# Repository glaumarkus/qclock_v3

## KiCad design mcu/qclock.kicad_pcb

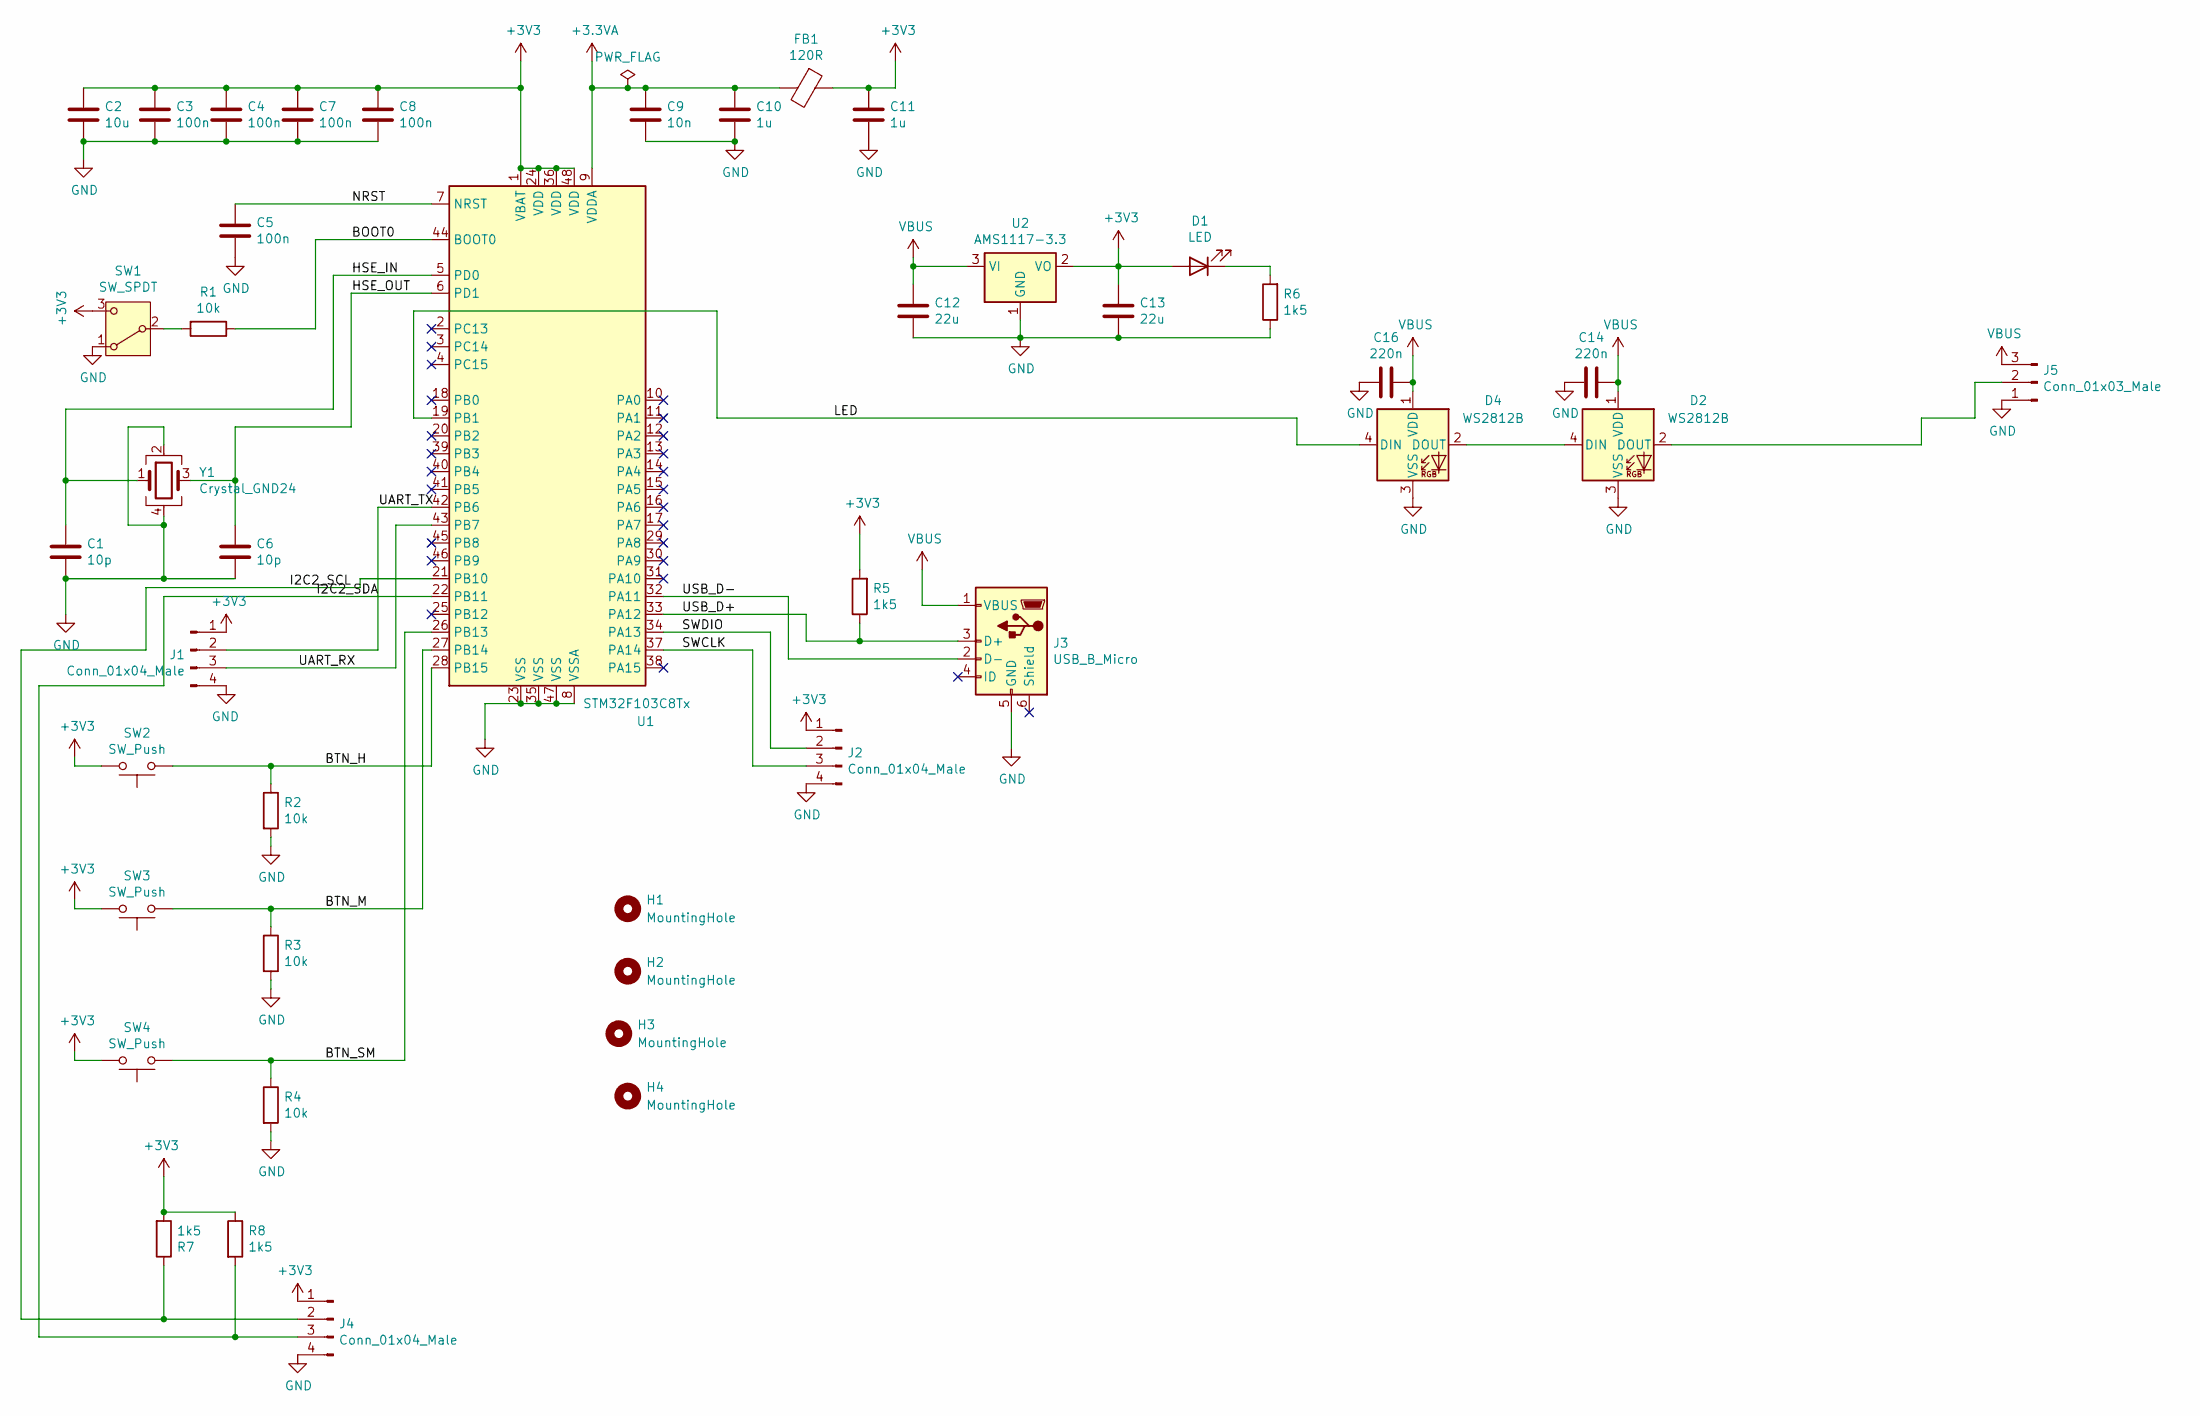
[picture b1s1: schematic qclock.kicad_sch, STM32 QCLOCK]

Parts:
C1, C6: 10p; C_0402_1005Metric
C2: 10u; C_0603_1608Metric
C3, C4, C5, C7, C8: 100n; C_0402_1005Metric
C9: 10n; C_0402_1005Metric
C10, C11: 1u; C_0402_1005Metric
C12, C13: 22u; C_0805_2012Metric
C14, C16: 220n; C_0402_1005Metric
D1: LED; LED_0603_1608Metric; JLCPCB Part #（optional） C2290
D2, D4: WS2812B; LED_WS2812B_PLCC4_5.0x5.0mm_P3.2mm; JLCPCB Part #（optional） C2846931
FB1: 120R; L_0402_1005Metric; JLCPCB Part #（optional） C3015760
H1, H2, H3, H4: MountingHole; MountingHole_2.2mm_M2
J1, J2, J4: Conn_01x04_Male; PinHeader_1x04_P2.54mm_Vertical
J3: USB_B_Micro; CUS-12TB_NDC; JLCPCB Part #（optional） C40943
J5: Conn_01x03_Male; PinHeader_1x03_P2.54mm_Vertical
R1, R2, R3, R4: 10k; R_0402_1005Metric; JLCPCB Part #（optional） C25744
R5, R6, R7, R8: 1k5; R_0402_1005Metric
SW1: SW_SPDT; CUS-12TB_NDC; JLCPCB Part #（optional） C2921739
SW2, SW3, SW4: SW_Push; mybtn_smd; JLCPCB Part #（optional） C455109
U1: STM32F103C8Tx; LQFP-48_7x7mm_P0.5mm
U2: AMS1117-3.3; SOT-223-3_TabPin2
Y1: Crystal_GND24; Crystal_SMD_3225-4Pin_3.2x2.5mm; JLCPCB Part #（optional） C963553

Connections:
+3.3VA: C9.1, C10.1, FB1.2, U1.9 (VDDA)
+3V3: C2.1, C3.1, C4.1, C7.1, C8.1, C11.1, C13.1, D1.2 (A), FB1.1, J1.1, J2.1, J4.1, R5.2, R7.2, R8.1, SW1.3 (C), SW2.2, SW3.2, SW4.2, U1.1 (VBAT), U1.24 (VDD), U1.36 (VDD), U1.48 (VDD), U2.2 (VO)
/BOOT0: R1.1, U1.44 (BOOT0)
/BTN_H: R2.1, SW2.1, U1.28 (PB15)
/BTN_M: R3.1, SW3.1, U1.27 (PB14)
/BTN_SM: R4.1, SW4.1, U1.26 (PB13)
/HSE_IN: C1.1, U1.5 (PD0), Y1.1
/HSE_OUT: C6.1, U1.6 (PD1), Y1.3
/I2C2_SCL: J4.2, R7.1, U1.21 (PB10)
/I2C2_SDA: J4.3, R8.2, U1.22 (PB11)
/LED: D4.4 (DIN), U1.19 (PB1)
/NRST: C5.1, U1.7 (NRST)
/SWCLK: J2.3, U1.37 (PA14)
/SWDIO: J2.2, U1.34 (PA13)
/UART_RX: J1.3, U1.43 (PB7)
/UART_TX: J1.2, U1.42 (PB6)
/USB_D+: J3.3 (D+), R5.1, U1.33 (PA12)
/USB_D-: J3.2 (D-), U1.32 (PA11)
GND: C1.2, C2.2, C3.2, C4.2, C5.2, C6.2, C7.2, C8.2, C9.2, C10.2, C11.2, C12.2, C13.2, C14.2, C16.2, D2.3 (VSS), D4.3 (VSS), J1.4, J2.4, J3.5 (GND), J4.4, J5.1, R2.2, R3.2, R4.2, R6.1, SW1.1 (A), U1.8 (VSSA), U1.23 (VSS), U1.35 (VSS), U1.47 (VSS), U2.1 (GND), Y1.2, Y1.4
unnamed: D1.1 (K), R6.2
unnamed: D2.4 (DIN), D4.2 (DOUT)
unnamed: D2.2 (DOUT), J5.2
unnamed: R1.2, SW1.2 (B)
VBUS: C12.1, C14.1, C16.1, D2.1 (VDD), D4.1 (VDD), J3.1 (VBUS), J5.3, U2.3 (VI)

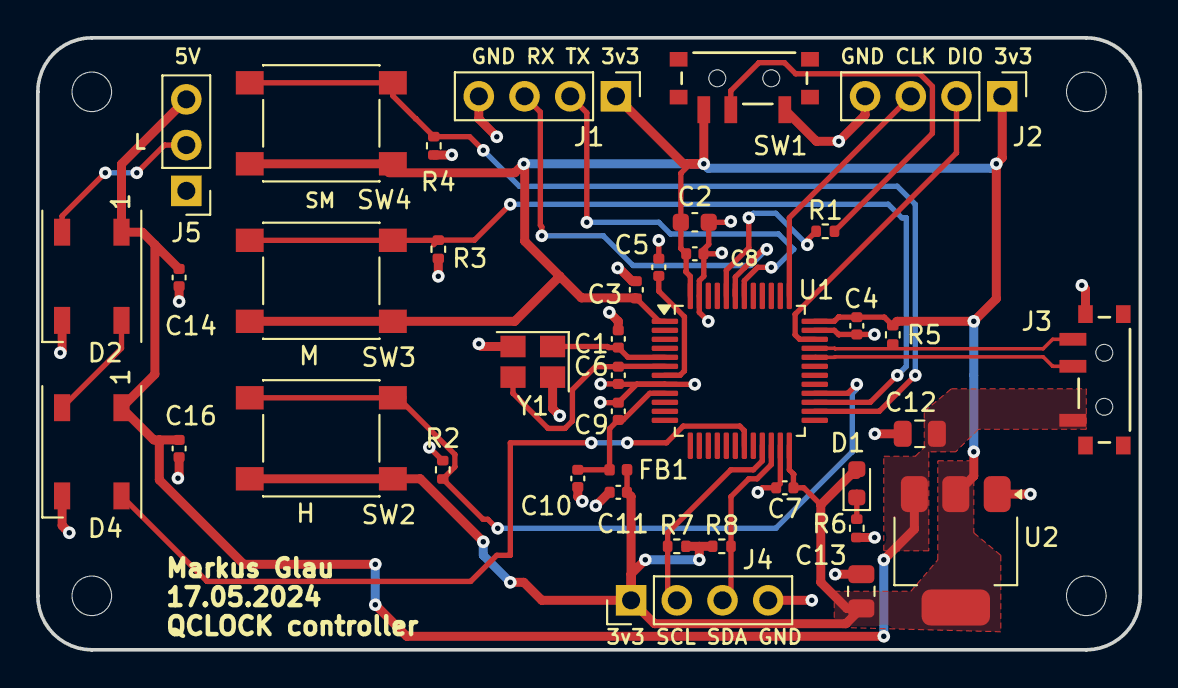
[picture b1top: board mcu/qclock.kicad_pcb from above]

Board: 2 copper layers, 61.2 x 34.0 mm, 43 parts (0 on the bottom side), 24 nets.

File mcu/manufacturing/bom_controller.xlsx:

Comment | Designator | Footprint | JLCPCB Part #（optional）
Crystal_GND24 | Y1 | Crystal:Crystal_SMD_3225-4Pin_3.2x2.5mm | C963553
AMS1117-3.3 | U2 | Package_TO_SOT_SMD:SOT-223-3_TabPin2
STM32F103C8Tx | U1 | Package_QFP:LQFP-48_7x7mm_P0.5mm
SW_Push | SW2,SW3,SW4 | btns:mybtn_smd | C455109
SW_SPDT | SW1 | footprints:CUS-12TB_NDC | C2921739
1k5 | R5,R6,R7,R8 | Resistor_SMD:R_0402_1005Metric
10k | R1,R2,R3,R4 | Resistor_SMD:R_0402_1005Metric | C25744
Conn_01x03_Male | J5 | Connector_PinHeader_2.54mm:PinHeader_1x03_P2.54mm_Vertical
USB_B_Micro | J3 | Connector_USB:USB_Micro-B_Wuerth_629105150521 | C879727
Conn_01x04_Male | J1,J2,J4 | Connector_PinHeader_2.54mm:PinHeader_1x04_P2.54mm_Vertical
120R | FB1 | Inductor_SMD:L_0402_1005Metric | C3015760
WS2812B | D2,D4 | LED_SMD:LED_WS2812B_PLCC4_5.0x5.0mm_P3.2mm | C2846931
LED | D1 | LED_SMD:LED_0603_1608Metric | C2290
220n | C14,C16 | Capacitor_SMD:C_0402_1005Metric
22u | C12,C13 | Capacitor_SMD:C_0805_2012Metric
1u | C10,C11 | Capacitor_SMD:C_0402_1005Metric
10n | C9 | Capacitor_SMD:C_0402_1005Metric
100n | C3,C4,C5,C7,C8 | Capacitor_SMD:C_0402_1005Metric
10u | C2 | Capacitor_SMD:C_0603_1608Metric
10p | C1,C6 | Capacitor_SMD:C_0402_1005Metric

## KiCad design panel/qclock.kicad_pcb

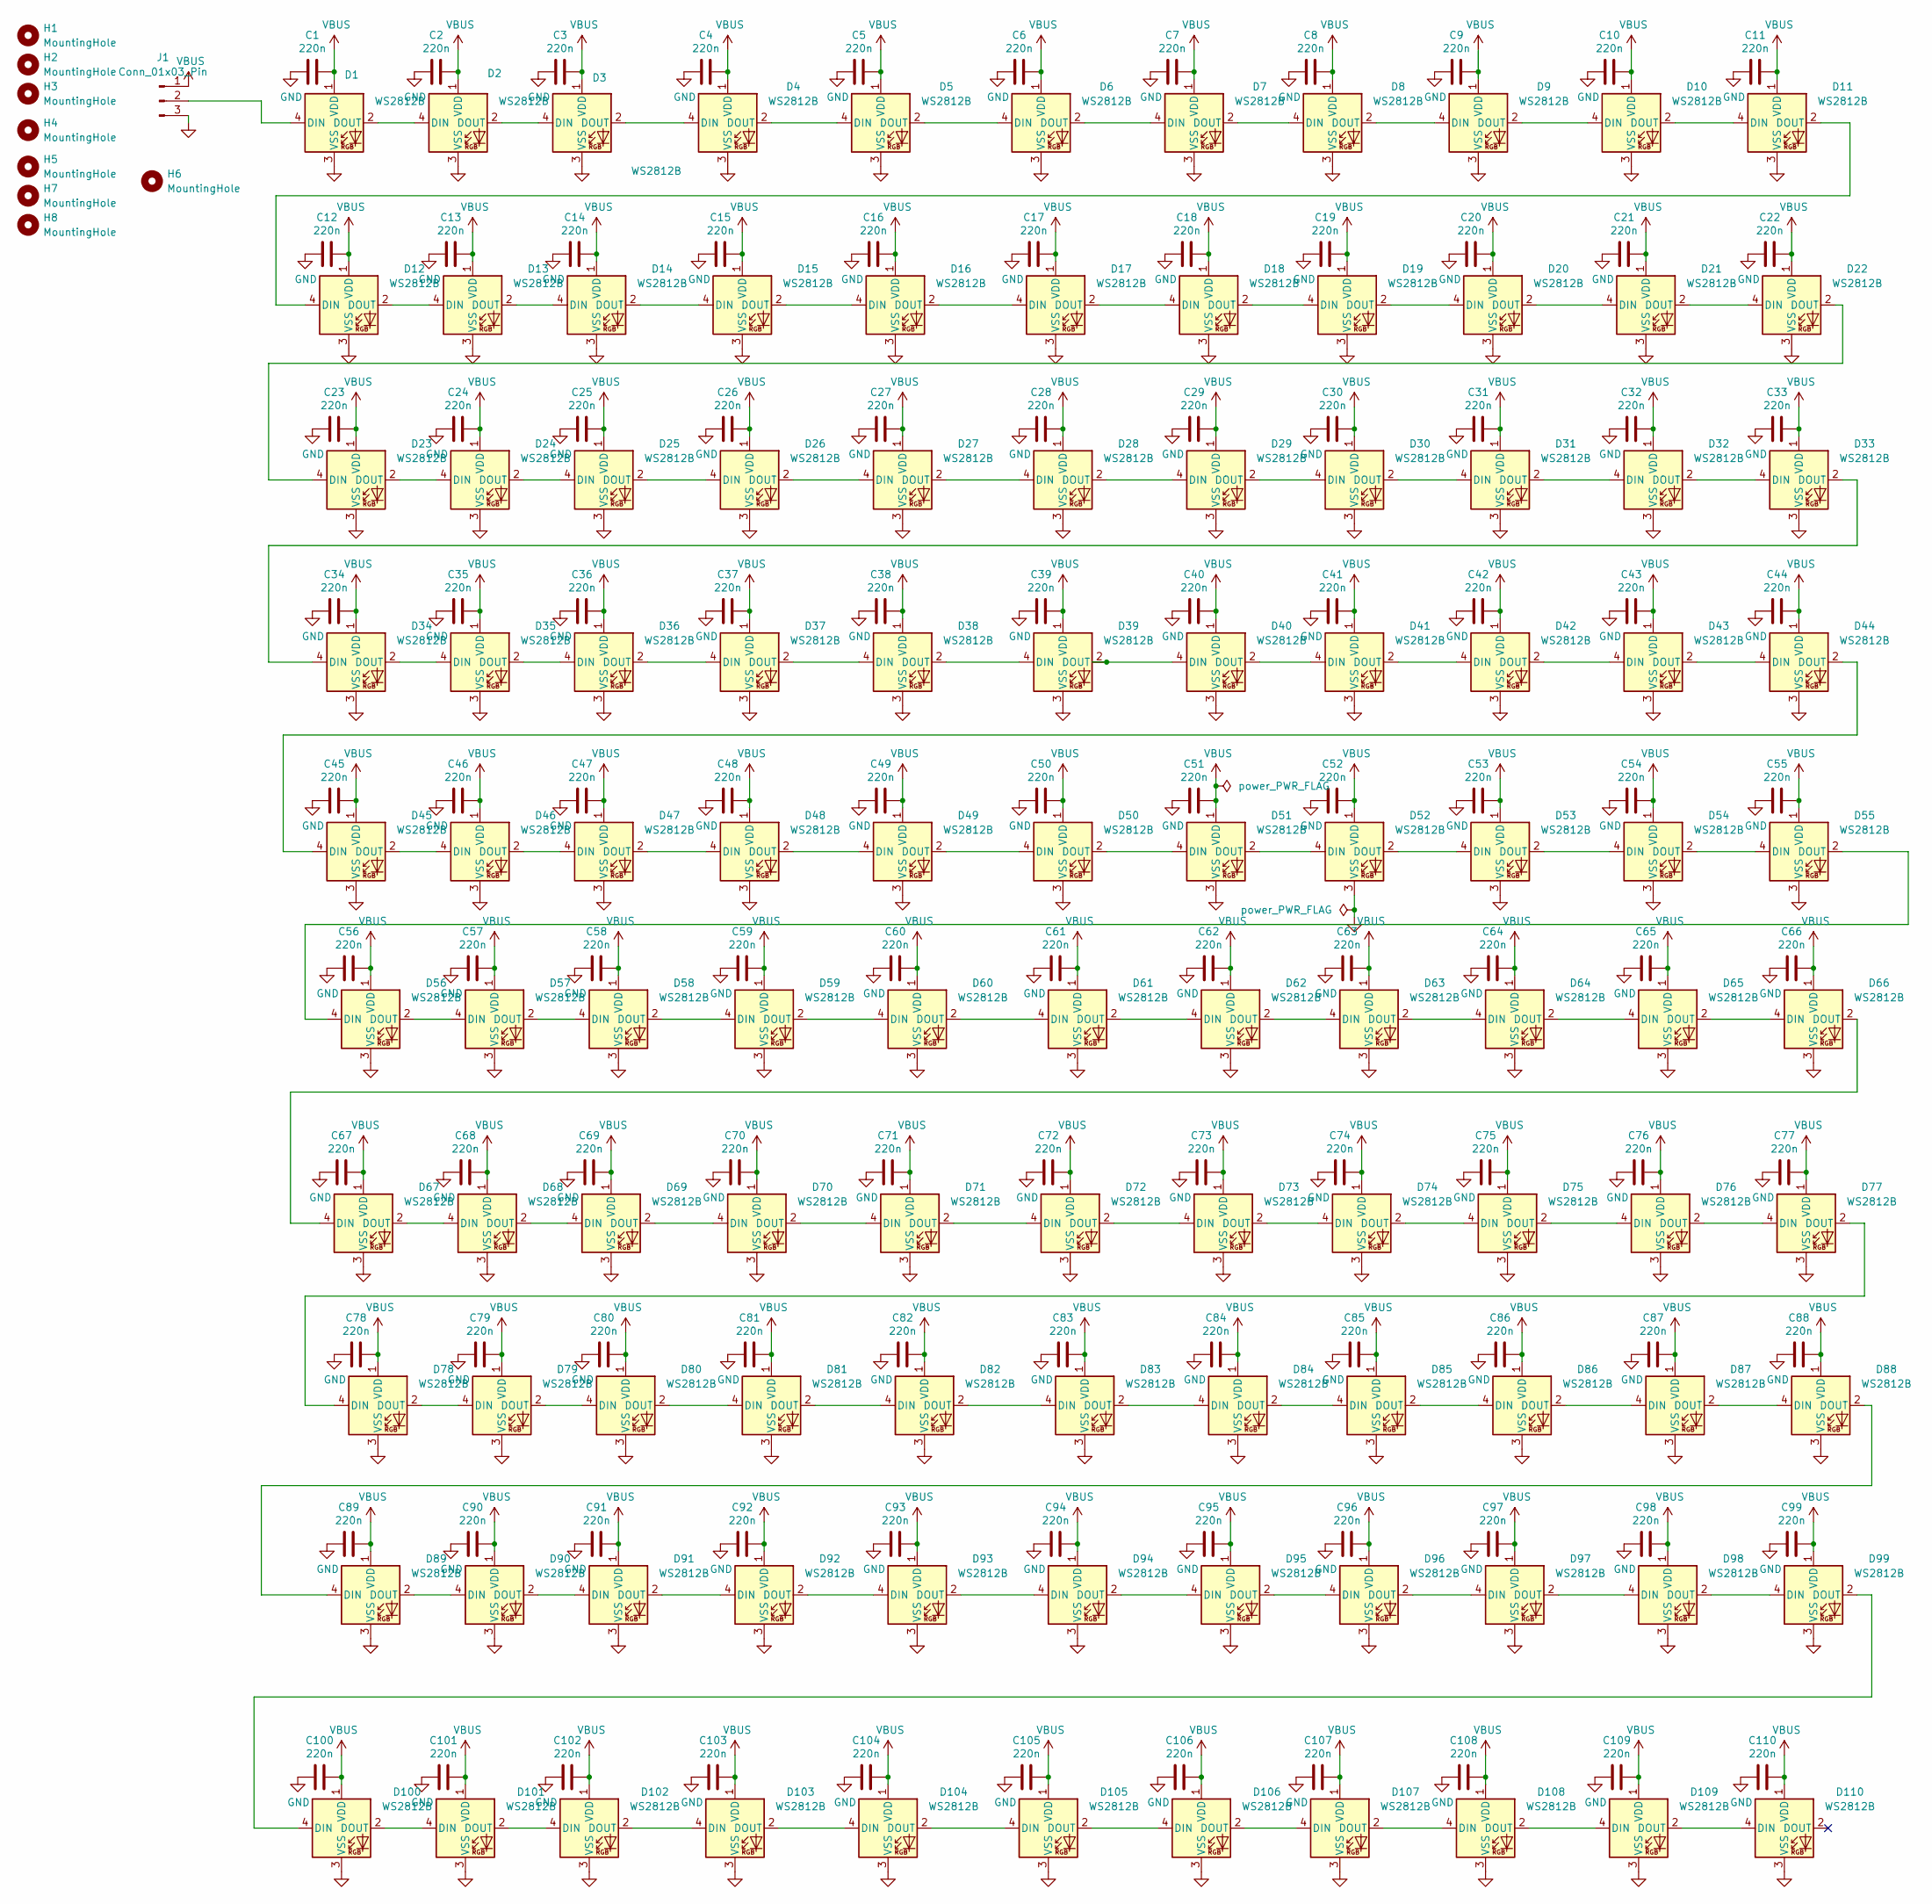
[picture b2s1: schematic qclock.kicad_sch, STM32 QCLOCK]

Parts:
C1, C2, C3, C4, C5, C6, C7, C8, C9, C10, C11, C12, C13, C14, C15, C16, C17, C18, C19, C20, C21, C22, C23, C24, C25, C26, C27, C28, C29, C30, C31, C32, C33, C34, C35, C36, C37, C38, C39, C40, C41, C42, C43, C44, C45, C46, C47, C48, C49, C50, C51, C52, C53, C54, C55, C56, C57, C58, C59, C60, C61, C62, C63, C64, C65, C66, C67, C68, C69, C70, C71, C72, C73, C74, C75, C76, C77, C78, C79, C80, C81, C82, C83, C84, C85, C86, C87, C88, C89, C90, C91, C92, C93, C94, C95, C96, C97, C98, C99, C100, C101, C102, C103, C104, C105, C106, C107, C108, C109, C110: 220n; C_0402_1005Metric
D1, D2, D3, D4, D5, D6, D7, D8, D9, D10, D11, D12, D13, D14, D15, D16, D17, D18, D19, D20, D21, D22, D23, D24, D25, D26, D27, D28, D29, D30, D31, D32, D33, D34, D35, D36, D37, D38, D39, D40, D41, D42, D43, D44, D45, D46, D47, D48, D49, D50, D51, D52, D53, D54, D55, D56, D57, D58, D59, D60, D61, D62, D63, D64, D65, D66, D67, D68, D69, D70, D71, D72, D73, D74, D75, D76, D77, D78, D79, D80, D81, D82, D83, D84, D85, D86, D87, D88, D89, D90, D91, D92, D93, D94, D95, D96, D97, D98, D99, D100, D101, D102, D103, D104, D105, D106, D107, D108, D109, D110: WS2812B; LED_WS2812B_PLCC4_5.0x5.0mm_P3.2mm
H1, H2, H3, H4: MountingHole; MountingHole_2.2mm_M2
H5, H6, H7, H8: MountingHole; MountingHole_3.2mm_M3
J1: Conn_01x03_Pin; PinHeader_1x03_P2.54mm_Horizontal

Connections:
GND: C1.2, C2.2, C3.2, C4.2, C5.2, C6.2, C7.2, C8.2, C9.2, C10.2, C11.2, C12.2, C13.2, C14.2, C15.2, C16.2, C17.2, C18.2, C19.2, C20.2, C21.2, C22.2, C23.2, C24.2, C25.2, C26.2, C27.2, C28.2, C29.2, C30.2, C31.2, C32.2, C33.2, C34.2, C35.2, C36.2, C37.2, C38.2, C39.2, C40.2, C41.2, C42.2, C43.2, C44.2, C45.2, C46.2, C47.2, C48.2, C49.2, C50.2, C51.2, C52.2, C53.2, C54.2, C55.2, C56.2, C57.2, C58.2, C59.2, C60.2, C61.2, C62.2, C63.2, C64.2, C65.2, C66.2, C67.2, C68.2, C69.2, C70.2, C71.2, C72.2, C73.2, C74.2, C75.2, C76.2, C77.2, C78.2, C79.2, C80.2, C81.2, C82.2, C83.2, C84.2, C85.2, C86.2, C87.2, C88.2, C89.2, C90.2, C91.2, C92.2, C93.2, C94.2, C95.2, C96.2, C97.2, C98.2, C99.2, C100.2, C101.2, C102.2, C103.2, C104.2, C105.2, C106.2, C107.2, C108.2, C109.2, C110.2, D1.3 (VSS), D2.3 (VSS), D3.3 (VSS), D4.3 (VSS), D5.3 (VSS), D6.3 (VSS), D7.3 (VSS), D8.3 (VSS), D9.3 (VSS), D10.3 (VSS), D11.3 (VSS), D12.3 (VSS), D13.3 (VSS), D14.3 (VSS), D15.3 (VSS), D16.3 (VSS), D17.3 (VSS), D18.3 (VSS), D19.3 (VSS), D20.3 (VSS), D21.3 (VSS), D22.3 (VSS), D23.3 (VSS), D24.3 (VSS), D25.3 (VSS), D26.3 (VSS), D27.3 (VSS), D28.3 (VSS), D29.3 (VSS), D30.3 (VSS), D31.3 (VSS), D32.3 (VSS), D33.3 (VSS), D34.3 (VSS), D35.3 (VSS), D36.3 (VSS), D37.3 (VSS), D38.3 (VSS), D39.3 (VSS), D40.3 (VSS), D41.3 (VSS), D42.3 (VSS), D43.3 (VSS), D44.3 (VSS), D45.3 (VSS), D46.3 (VSS), D47.3 (VSS), D48.3 (VSS), D49.3 (VSS), D50.3 (VSS), D51.3 (VSS), D52.3 (VSS), D53.3 (VSS), D54.3 (VSS), D55.3 (VSS), D56.3 (VSS), D57.3 (VSS), D58.3 (VSS), D59.3 (VSS), D60.3 (VSS), D61.3 (VSS), D62.3 (VSS), D63.3 (VSS), D64.3 (VSS), D65.3 (VSS), D66.3 (VSS), D67.3 (VSS), D68.3 (VSS), D69.3 (VSS), D70.3 (VSS), D71.3 (VSS), D72.3 (VSS), D73.3 (VSS), D74.3 (VSS), D75.3 (VSS), D76.3 (VSS), D77.3 (VSS), D78.3 (VSS), D79.3 (VSS), D80.3 (VSS), D81.3 (VSS), D82.3 (VSS), D83.3 (VSS), D84.3 (VSS), D85.3 (VSS), D86.3 (VSS), D87.3 (VSS), D88.3 (VSS), D89.3 (VSS), D90.3 (VSS), D91.3 (VSS), D92.3 (VSS), D93.3 (VSS), D94.3 (VSS), D95.3 (VSS), D96.3 (VSS), D97.3 (VSS), D98.3 (VSS), D99.3 (VSS), D100.3 (VSS), D101.3 (VSS), D102.3 (VSS), D103.3 (VSS), D104.3 (VSS), D105.3 (VSS), D106.3 (VSS), D107.3 (VSS), D108.3 (VSS), D109.3 (VSS), D110.3 (VSS), J1.3
unnamed: D1.4 (DIN), J1.2
unnamed: D1.2 (DOUT), D2.4 (DIN)
unnamed: D2.2 (DOUT), D3.4 (DIN)
unnamed: D3.2 (DOUT), D4.4 (DIN)
unnamed: D4.2 (DOUT), D5.4 (DIN)
unnamed: D5.2 (DOUT), D6.4 (DIN)
unnamed: D6.2 (DOUT), D7.4 (DIN)
unnamed: D7.2 (DOUT), D8.4 (DIN)
unnamed: D8.2 (DOUT), D9.4 (DIN)
unnamed: D9.2 (DOUT), D10.4 (DIN)
unnamed: D10.2 (DOUT), D11.4 (DIN)
unnamed: D11.2 (DOUT), D12.4 (DIN)
unnamed: D12.2 (DOUT), D13.4 (DIN)
unnamed: D13.2 (DOUT), D14.4 (DIN)
unnamed: D14.2 (DOUT), D15.4 (DIN)
unnamed: D15.2 (DOUT), D16.4 (DIN)
unnamed: D16.2 (DOUT), D17.4 (DIN)
unnamed: D17.2 (DOUT), D18.4 (DIN)
unnamed: D18.2 (DOUT), D19.4 (DIN)
unnamed: D19.2 (DOUT), D20.4 (DIN)
unnamed: D20.2 (DOUT), D21.4 (DIN)
unnamed: D21.2 (DOUT), D22.4 (DIN)
unnamed: D22.2 (DOUT), D23.4 (DIN)
unnamed: D23.2 (DOUT), D24.4 (DIN)
unnamed: D24.2 (DOUT), D25.4 (DIN)
unnamed: D25.2 (DOUT), D26.4 (DIN)
unnamed: D26.2 (DOUT), D27.4 (DIN)
unnamed: D27.2 (DOUT), D28.4 (DIN)
unnamed: D28.2 (DOUT), D29.4 (DIN)
unnamed: D29.2 (DOUT), D30.4 (DIN)
unnamed: D30.2 (DOUT), D31.4 (DIN)
unnamed: D31.2 (DOUT), D32.4 (DIN)
unnamed: D32.2 (DOUT), D33.4 (DIN)
unnamed: D33.2 (DOUT), D34.4 (DIN)
unnamed: D34.2 (DOUT), D35.4 (DIN)
unnamed: D35.2 (DOUT), D36.4 (DIN)
unnamed: D36.2 (DOUT), D37.4 (DIN)
unnamed: D37.2 (DOUT), D38.4 (DIN)
unnamed: D38.2 (DOUT), D39.4 (DIN)
unnamed: D39.2 (DOUT), D40.4 (DIN)
unnamed: D40.2 (DOUT), D41.4 (DIN)
unnamed: D41.2 (DOUT), D42.4 (DIN)
unnamed: D42.2 (DOUT), D43.4 (DIN)
unnamed: D43.2 (DOUT), D44.4 (DIN)
unnamed: D44.2 (DOUT), D45.4 (DIN)
unnamed: D45.2 (DOUT), D46.4 (DIN)
unnamed: D46.2 (DOUT), D47.4 (DIN)
unnamed: D47.2 (DOUT), D48.4 (DIN)
unnamed: D48.2 (DOUT), D49.4 (DIN)
unnamed: D49.2 (DOUT), D50.4 (DIN)
unnamed: D50.2 (DOUT), D51.4 (DIN)
unnamed: D51.2 (DOUT), D52.4 (DIN)
unnamed: D52.2 (DOUT), D53.4 (DIN)
unnamed: D53.2 (DOUT), D54.4 (DIN)
unnamed: D54.2 (DOUT), D55.4 (DIN)
unnamed: D55.2 (DOUT), D56.4 (DIN)
unnamed: D56.2 (DOUT), D57.4 (DIN)
unnamed: D57.2 (DOUT), D58.4 (DIN)
unnamed: D58.2 (DOUT), D59.4 (DIN)
unnamed: D59.2 (DOUT), D60.4 (DIN)
unnamed: D60.2 (DOUT), D61.4 (DIN)
unnamed: D61.2 (DOUT), D62.4 (DIN)
unnamed: D62.2 (DOUT), D63.4 (DIN)
unnamed: D63.2 (DOUT), D64.4 (DIN)
unnamed: D64.2 (DOUT), D65.4 (DIN)
unnamed: D65.2 (DOUT), D66.4 (DIN)
unnamed: D66.2 (DOUT), D67.4 (DIN)
unnamed: D67.2 (DOUT), D68.4 (DIN)
unnamed: D68.2 (DOUT), D69.4 (DIN)
unnamed: D69.2 (DOUT), D70.4 (DIN)
unnamed: D70.2 (DOUT), D71.4 (DIN)
unnamed: D71.2 (DOUT), D72.4 (DIN)
unnamed: D72.2 (DOUT), D73.4 (DIN)
unnamed: D73.2 (DOUT), D74.4 (DIN)
unnamed: D74.2 (DOUT), D75.4 (DIN)
unnamed: D75.2 (DOUT), D76.4 (DIN)
unnamed: D76.2 (DOUT), D77.4 (DIN)
unnamed: D77.2 (DOUT), D78.4 (DIN)
unnamed: D78.2 (DOUT), D79.4 (DIN)
unnamed: D79.2 (DOUT), D80.4 (DIN)
unnamed: D80.2 (DOUT), D81.4 (DIN)
unnamed: D81.2 (DOUT), D82.4 (DIN)
unnamed: D82.2 (DOUT), D83.4 (DIN)
unnamed: D83.2 (DOUT), D84.4 (DIN)
unnamed: D84.2 (DOUT), D85.4 (DIN)
unnamed: D85.2 (DOUT), D86.4 (DIN)
unnamed: D86.2 (DOUT), D87.4 (DIN)
unnamed: D87.2 (DOUT), D88.4 (DIN)
unnamed: D88.2 (DOUT), D89.4 (DIN)
unnamed: D89.2 (DOUT), D90.4 (DIN)
unnamed: D90.2 (DOUT), D91.4 (DIN)
unnamed: D91.2 (DOUT), D92.4 (DIN)
unnamed: D92.2 (DOUT), D93.4 (DIN)
unnamed: D93.2 (DOUT), D94.4 (DIN)
unnamed: D94.2 (DOUT), D95.4 (DIN)
unnamed: D95.2 (DOUT), D96.4 (DIN)
unnamed: D96.2 (DOUT), D97.4 (DIN)
unnamed: D97.2 (DOUT), D98.4 (DIN)
unnamed: D98.2 (DOUT), D99.4 (DIN)
unnamed: D99.2 (DOUT), D100.4 (DIN)
unnamed: D100.2 (DOUT), D101.4 (DIN)
unnamed: D101.2 (DOUT), D102.4 (DIN)
unnamed: D102.2 (DOUT), D103.4 (DIN)
unnamed: D103.2 (DOUT), D104.4 (DIN)
unnamed: D104.2 (DOUT), D105.4 (DIN)
unnamed: D105.2 (DOUT), D106.4 (DIN)
unnamed: D106.2 (DOUT), D107.4 (DIN)
unnamed: D107.2 (DOUT), D108.4 (DIN)
unnamed: D108.2 (DOUT), D109.4 (DIN)
unnamed: D109.2 (DOUT), D110.4 (DIN)
VBUS: C1.1, C2.1, C3.1, C4.1, C5.1, C6.1, C7.1, C8.1, C9.1, C10.1, C11.1, C12.1, C13.1, C14.1, C15.1, C16.1, C17.1, C18.1, C19.1, C20.1, C21.1, C22.1, C23.1, C24.1, C25.1, C26.1, C27.1, C28.1, C29.1, C30.1, C31.1, C32.1, C33.1, C34.1, C35.1, C36.1, C37.1, C38.1, C39.1, C40.1, C41.1, C42.1, C43.1, C44.1, C45.1, C46.1, C47.1, C48.1, C49.1, C50.1, C51.1, C52.1, C53.1, C54.1, C55.1, C56.1, C57.1, C58.1, C59.1, C60.1, C61.1, C62.1, C63.1, C64.1, C65.1, C66.1, C67.1, C68.1, C69.1, C70.1, C71.1, C72.1, C73.1, C74.1, C75.1, C76.1, C77.1, C78.1, C79.1, C80.1, C81.1, C82.1, C83.1, C84.1, C85.1, C86.1, C87.1, C88.1, C89.1, C90.1, C91.1, C92.1, C93.1, C94.1, C95.1, C96.1, C97.1, C98.1, C99.1, C100.1, C101.1, C102.1, C103.1, C104.1, C105.1, C106.1, C107.1, C108.1, C109.1, C110.1, D1.1 (VDD), D2.1 (VDD), D3.1 (VDD), D4.1 (VDD), D5.1 (VDD), D6.1 (VDD), D7.1 (VDD), D8.1 (VDD), D9.1 (VDD), D10.1 (VDD), D11.1 (VDD), D12.1 (VDD), D13.1 (VDD), D14.1 (VDD), D15.1 (VDD), D16.1 (VDD), D17.1 (VDD), D18.1 (VDD), D19.1 (VDD), D20.1 (VDD), D21.1 (VDD), D22.1 (VDD), D23.1 (VDD), D24.1 (VDD), D25.1 (VDD), D26.1 (VDD), D27.1 (VDD), D28.1 (VDD), D29.1 (VDD), D30.1 (VDD), D31.1 (VDD), D32.1 (VDD), D33.1 (VDD), D34.1 (VDD), D35.1 (VDD), D36.1 (VDD), D37.1 (VDD), D38.1 (VDD), D39.1 (VDD), D40.1 (VDD), D41.1 (VDD), D42.1 (VDD), D43.1 (VDD), D44.1 (VDD), D45.1 (VDD), D46.1 (VDD), D47.1 (VDD), D48.1 (VDD), D49.1 (VDD), D50.1 (VDD), D51.1 (VDD), D52.1 (VDD), D53.1 (VDD), D54.1 (VDD), D55.1 (VDD), D56.1 (VDD), D57.1 (VDD), D58.1 (VDD), D59.1 (VDD), D60.1 (VDD), D61.1 (VDD), D62.1 (VDD), D63.1 (VDD), D64.1 (VDD), D65.1 (VDD), D66.1 (VDD), D67.1 (VDD), D68.1 (VDD), D69.1 (VDD), D70.1 (VDD), D71.1 (VDD), D72.1 (VDD), D73.1 (VDD), D74.1 (VDD), D75.1 (VDD), D76.1 (VDD), D77.1 (VDD), D78.1 (VDD), D79.1 (VDD), D80.1 (VDD), D81.1 (VDD), D82.1 (VDD), D83.1 (VDD), D84.1 (VDD), D85.1 (VDD), D86.1 (VDD), D87.1 (VDD), D88.1 (VDD), D89.1 (VDD), D90.1 (VDD), D91.1 (VDD), D92.1 (VDD), D93.1 (VDD), D94.1 (VDD), D95.1 (VDD), D96.1 (VDD), D97.1 (VDD), D98.1 (VDD), D99.1 (VDD), D100.1 (VDD), D101.1 (VDD), D102.1 (VDD), D103.1 (VDD), D104.1 (VDD), D105.1 (VDD), D106.1 (VDD), D107.1 (VDD), D108.1 (VDD), D109.1 (VDD), D110.1 (VDD), J1.1

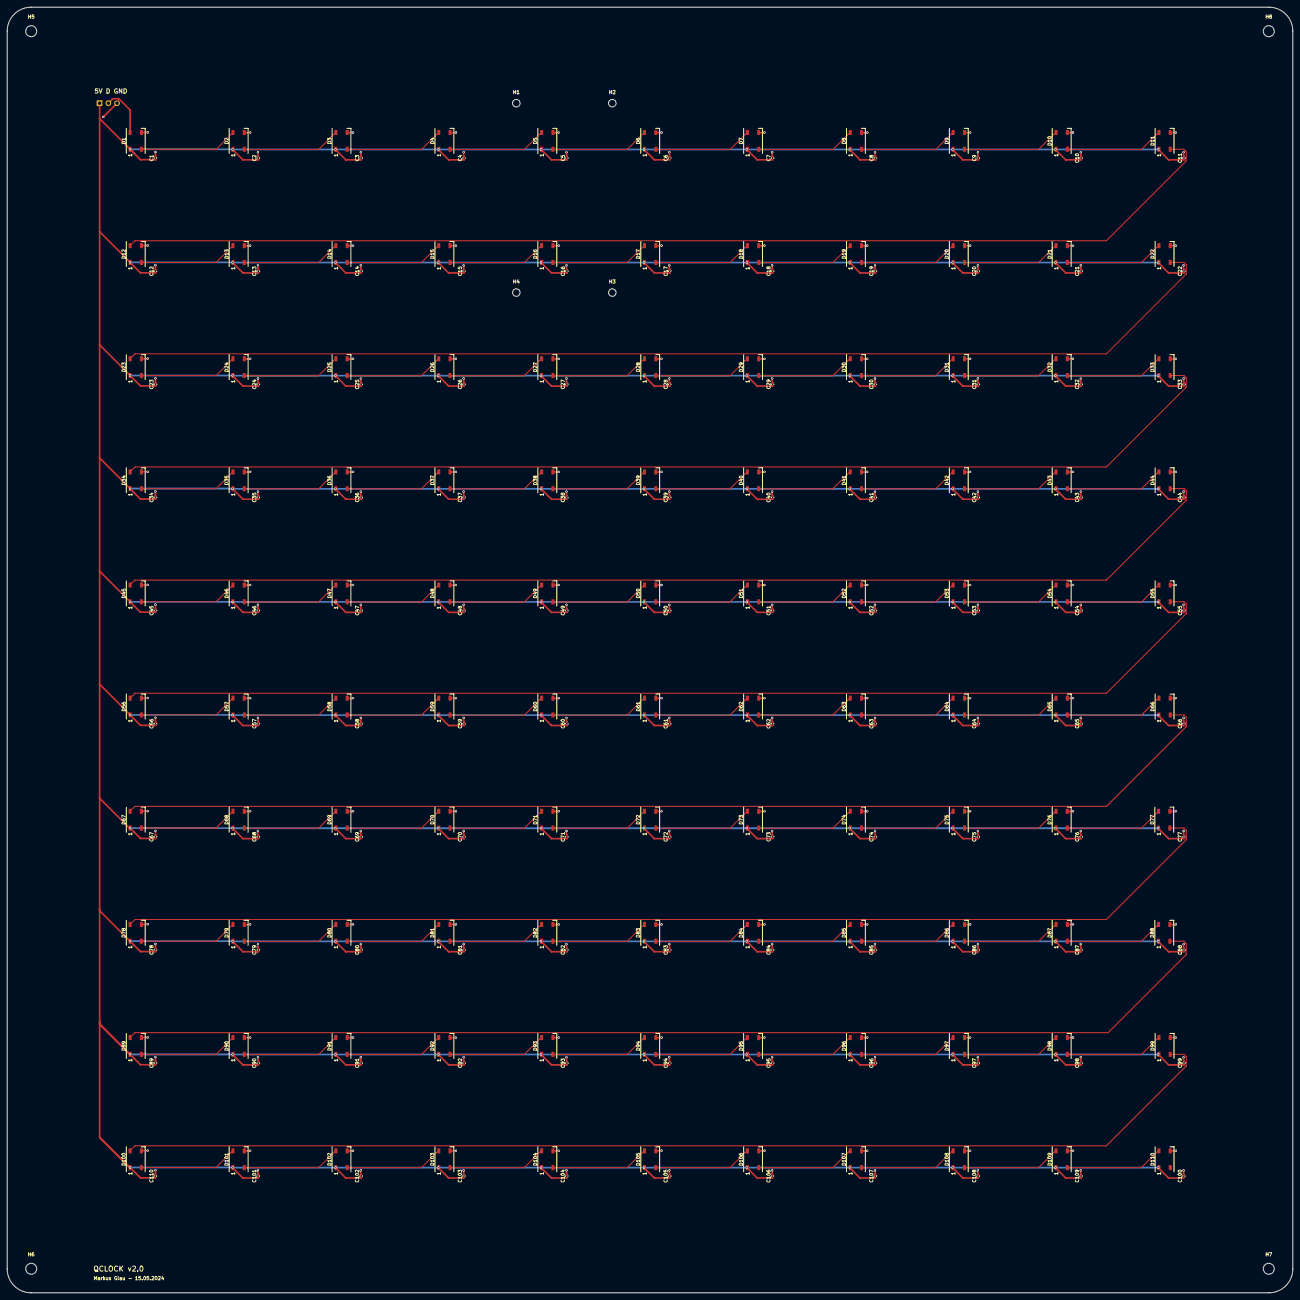
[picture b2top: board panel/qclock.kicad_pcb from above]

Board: 2 copper layers, 375.0 x 375.0 mm, 229 parts (1 on the bottom side), 112 nets.

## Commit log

2024-05-15 KiCad files
2024-05-16 Add poc
2024-05-16 PoC update
2024-05-17 Finish poc design
2024-05-17 Replace pos
2024-05-17 Add bom
2024-05-17 Redo files
2024-05-17 add xlsx
2024-05-18 Final models
2024-05-19 PCB design finished
2024-05-20 Update mcu
2024-05-20 add manufacturing files
